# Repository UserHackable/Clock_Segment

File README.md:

## Clock_Segment 

### Board dimensions

* (393701, 314961) original units
* (3.9370, 3.1496) inches
* (100.0001, 80.0001) mm

| Front | Back |
| --- | --- |
|  |  |

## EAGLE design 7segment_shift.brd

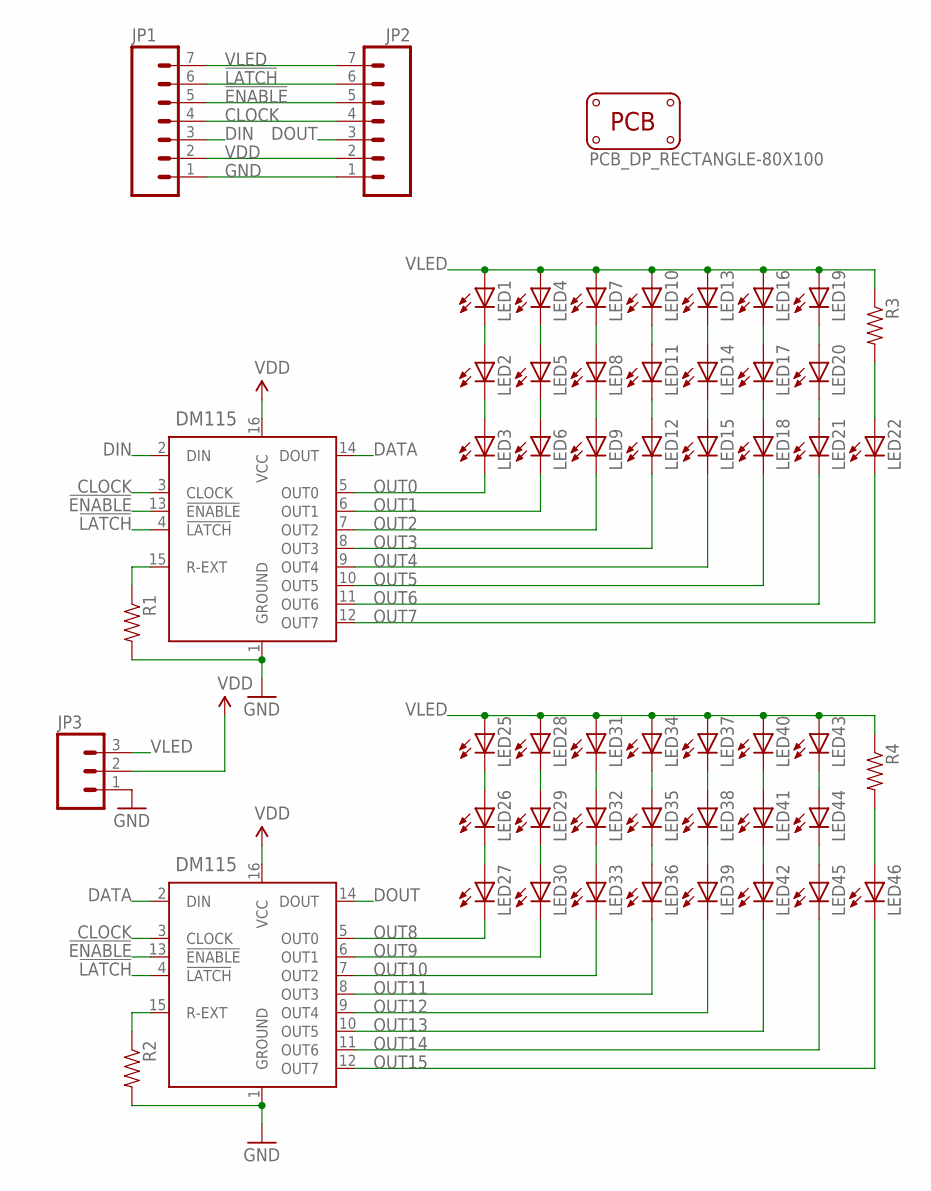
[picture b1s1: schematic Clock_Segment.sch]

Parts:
JP1, JP2: M07; 1X07
JP3: M03SCREW; SCREWTERMINAL-3.5MM-3
LED1, LED2, LED3, LED4, LED5, LED6, LED7, LED8, LED9, LED10, LED11, LED12, LED13, LED14, LED15, LED16, LED17, LED18, LED19, LED20, LED21, LED22, LED25, LED26, LED27, LED28, LED29, LED30, LED31, LED32, LED33, LED34, LED35, LED36, LED37, LED38, LED39, LED40, LED41, LED42, LED43, LED44, LED45, LED46: LEDOVAL; LED-OVAL
PCB1: PCB_DP_RECTANGLE-80X100; DP10080_V1
R1, R2, R3, R4: RESISTORAXIAL-0.3; AXIAL-0.3
U1, U2: DM115DIP16; DIL16

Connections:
!ENABLE: JP1.5, JP2.5, U1.13 (!ENABLE), U2.13 (!ENABLE)
!LATCH: JP1.6, JP2.6, U1.4 (!LATCH), U2.4 (!LATCH)
CLOCK: JP1.4, JP2.4, U1.3 (CLOCK), U2.3 (CLOCK)
DATA: U1.14 (DOUT), U2.2 (DIN)
DIN: JP1.3, U1.2 (DIN)
DOUT: JP2.3, U2.14 (DOUT)
GND: JP1.1, JP2.1, JP3.1, R1.P$2 (2), R2.P$2 (2), U1.1 (GROUND), U2.1 (GROUND)
unnamed: R1.P$1 (1), U1.15 (R-EXT)
unnamed: LED1.CATHODE (C), LED2.ANODE (A)
unnamed: LED2.CATHODE (C), LED3.ANODE (A)
unnamed: LED4.CATHODE (C), LED5.ANODE (A)
unnamed: LED5.CATHODE (C), LED6.ANODE (A)
unnamed: LED7.CATHODE (C), LED8.ANODE (A)
unnamed: LED8.CATHODE (C), LED9.ANODE (A)
unnamed: LED10.CATHODE (C), LED11.ANODE (A)
unnamed: LED11.CATHODE (C), LED12.ANODE (A)
unnamed: LED13.CATHODE (C), LED14.ANODE (A)
unnamed: LED14.CATHODE (C), LED15.ANODE (A)
unnamed: LED16.CATHODE (C), LED17.ANODE (A)
unnamed: LED17.CATHODE (C), LED18.ANODE (A)
unnamed: LED19.CATHODE (C), LED20.ANODE (A)
unnamed: LED20.CATHODE (C), LED21.ANODE (A)
unnamed: LED46.ANODE (A), R4.P$2 (2)
unnamed: R2.P$1 (1), U2.15 (R-EXT)
unnamed: LED25.CATHODE (C), LED26.ANODE (A)
unnamed: LED26.CATHODE (C), LED27.ANODE (A)
unnamed: LED28.CATHODE (C), LED29.ANODE (A)
unnamed: LED29.CATHODE (C), LED30.ANODE (A)
unnamed: LED31.CATHODE (C), LED32.ANODE (A)
unnamed: LED32.CATHODE (C), LED33.ANODE (A)
unnamed: LED34.CATHODE (C), LED35.ANODE (A)
unnamed: LED35.CATHODE (C), LED36.ANODE (A)
unnamed: LED37.CATHODE (C), LED38.ANODE (A)
unnamed: LED38.CATHODE (C), LED39.ANODE (A)
unnamed: LED40.CATHODE (C), LED41.ANODE (A)
unnamed: LED41.CATHODE (C), LED42.ANODE (A)
unnamed: LED43.CATHODE (C), LED44.ANODE (A)
unnamed: LED44.CATHODE (C), LED45.ANODE (A)
unnamed: LED22.ANODE (A), R3.P$2 (2)
OUT0: LED3.CATHODE (C), U1.5 (OUT0)
OUT1: LED6.CATHODE (C), U1.6 (OUT1)
OUT2: LED9.CATHODE (C), U1.7 (OUT2)
OUT3: LED12.CATHODE (C), U1.8 (OUT3)
OUT4: LED15.CATHODE (C), U1.9 (OUT4)
OUT5: LED18.CATHODE (C), U1.10 (OUT5)
OUT6: LED21.CATHODE (C), U1.11 (OUT6)
OUT7: LED22.CATHODE (C), U1.12 (OUT7)
OUT8: LED27.CATHODE (C), U2.5 (OUT0)
OUT9: LED30.CATHODE (C), U2.6 (OUT1)
OUT10: LED33.CATHODE (C), U2.7 (OUT2)
OUT11: LED36.CATHODE (C), U2.8 (OUT3)
OUT12: LED39.CATHODE (C), U2.9 (OUT4)
OUT13: LED42.CATHODE (C), U2.10 (OUT5)
OUT14: LED45.CATHODE (C), U2.11 (OUT6)
OUT15: LED46.CATHODE (C), U2.12 (OUT7)
VDD: JP1.2, JP2.2, JP3.2, U1.16 (VCC), U2.16 (VCC)
VLED: JP1.7, JP2.7, JP3.3, LED1.ANODE (A), LED4.ANODE (A), LED7.ANODE (A), LED10.ANODE (A), LED13.ANODE (A), LED16.ANODE (A), LED19.ANODE (A), LED25.ANODE (A), LED28.ANODE (A), LED31.ANODE (A), LED34.ANODE (A), LED37.ANODE (A), LED40.ANODE (A), LED43.ANODE (A), R3.P$1 (1), R4.P$1 (1)

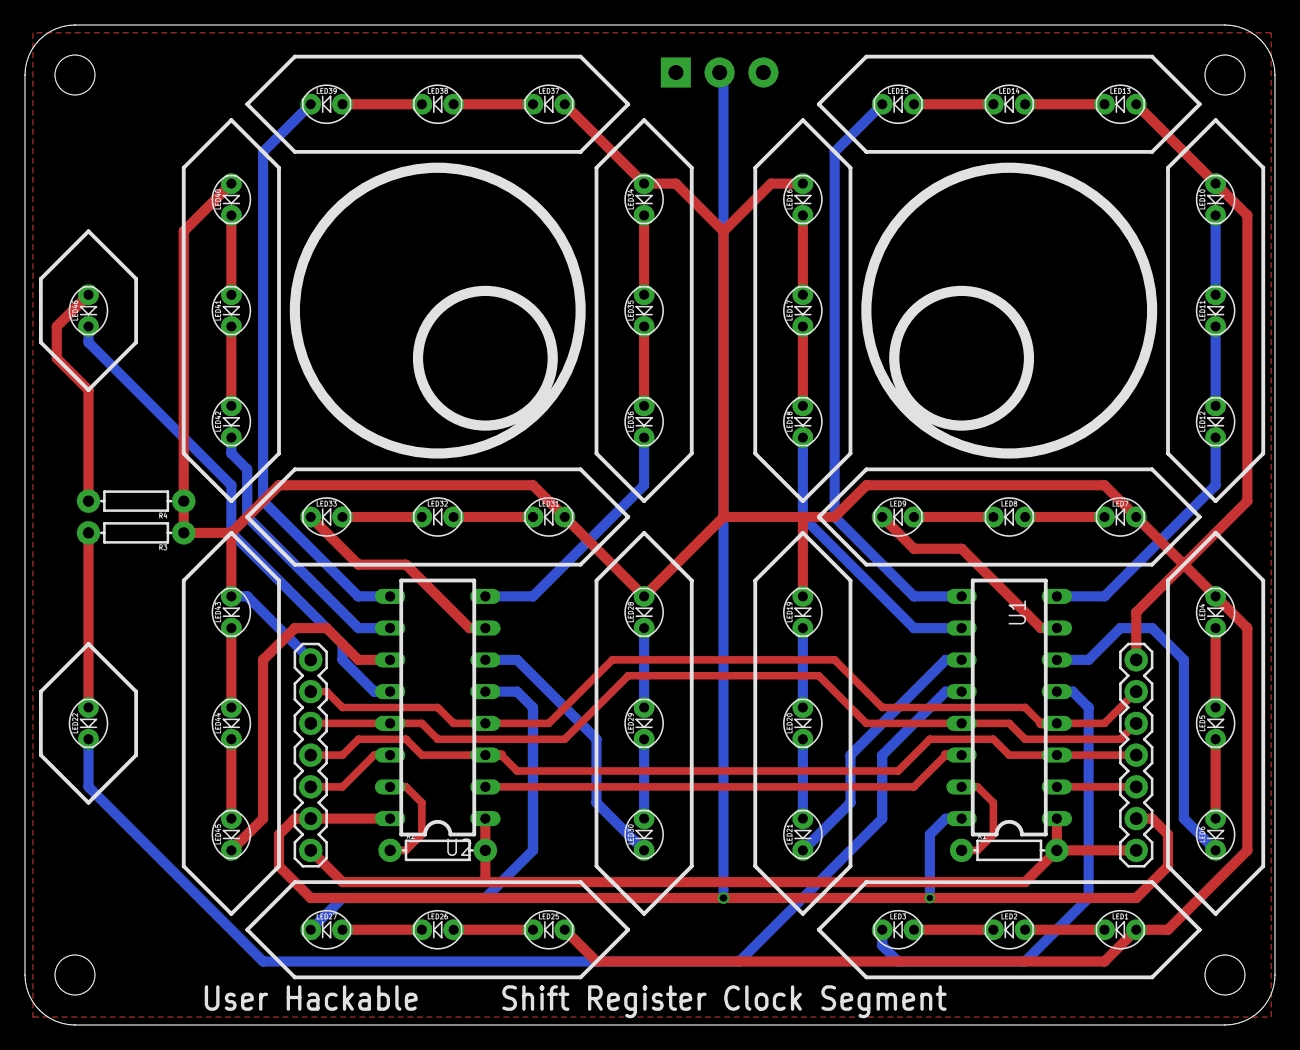
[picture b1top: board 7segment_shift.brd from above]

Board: 2 copper layers, 100.0 x 80.0 mm, 54 parts (1 on the bottom side), 57 nets.

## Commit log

2016-04-08 from Makefile
2016-04-08 cleanup files

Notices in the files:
parts and their libraries:
SparkFun-Connectors: Licensing: Creative Commons ShareAlike 4.0 International - https://creativecommons.org/licenses/by-sa/4.0
